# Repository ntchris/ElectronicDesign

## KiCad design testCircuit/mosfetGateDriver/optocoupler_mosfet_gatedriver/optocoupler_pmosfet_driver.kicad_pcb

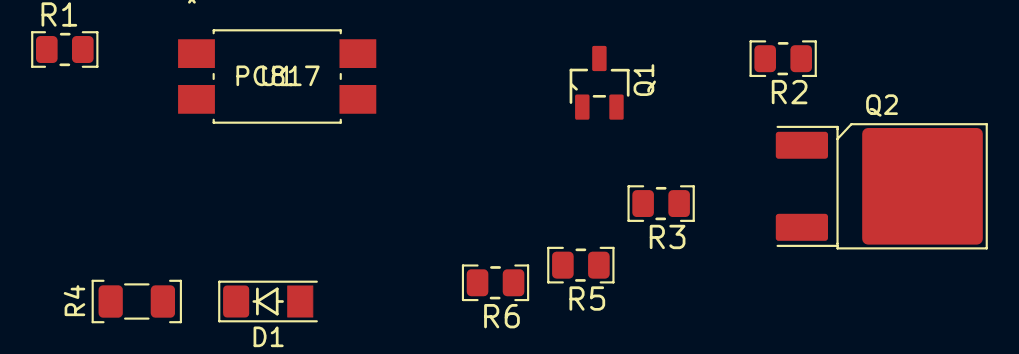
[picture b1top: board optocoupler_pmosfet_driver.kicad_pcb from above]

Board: 2 copper layers, 10 parts (0 on the bottom side), 9 nets, no tracks yet.

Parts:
D1: zener 5.1V; D_MiniMELF_Handsoldering_Zener
Q1: S9013; SOT-23_PNP_NPN
Q2: AOD403_pmosfet; TO-252-2
R1: 510; R_C_0805_2012Metric_Pad1.20x1.50mm_HandSolder
R2: 1.5k; R_C_0805_2012Metric_Pad1.20x1.50mm_HandSolder
R3: 20k; R_C_0805_2012Metric_Pad1.20x1.50mm_HandSolder
R4: 1.5k; R_C_1206_3216Metric_Pad1.33x1.80mm_HandSolder
R5: 800; R_C_0805_2012Metric_Pad1.20x1.50mm_HandSolder
R6: 10k; R_C_0805_2012Metric_Pad1.20x1.50mm_HandSolder
U1: PC817; EL817S1CTU-F

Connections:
/test_point_base: Q1.B, R3.1, U1.3
/test_point_gate: D1.1 (K), Q2.G, R2.1, R4.1
/test_point_load_power: Q2.D, R6.2
GND: Q1.E, R3.2, R6.1
unnamed: D1.2 (A), R5.2
unnamed: Q2.S, R4.2
unnamed: Q1.C, R5.1
unnamed: R1.1, U1.1
unnamed: R2.2, U1.4

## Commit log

2016-10-16 :lollipop: Added .gitattributes & .gitignore files
2017-01-27 submit all ee design
2017-02-04 done
2017-02-27 Finish TL494 design
2017-06-09 commit june 08 2017
2017-06-09 remove export svg
2017-06-09 fix pic
2017-06-09 pic update
2017-06-12 PCB rev2
2017-07-02 add tp5410 and tp4056 design
2017-07-03 5410 and 4056 to print
2017-07-06 folder reorg
2017-08-14 charge boot update
2017-08-27 tl494 new project
2017-08-27 aug27 design PCB finished
2017-08-28 minnor fix
2017-08-28 minor updat 2
2017-08-31 update pcb
2017-10-08 ip5306 charge boost project
2017-10-08 modify inductor 7mm foot print
2017-10-08 modify inductor 7 ver2
2017-10-08 modify inductor7 ver3
2017-10-08 pcb update
2017-10-08 pcb bottom
2017-10-12 IP5306 version 2
2017-10-12 update usb hole position
2017-10-26 add new project ne555 motor pwm controller
2017-10-29 fix the wrong ifrf1205 footprint (source must be ground pin3)
2017-11-05 FP6719_BoostQC submit
2017-11-16 update the cap and pcb
    larger cap in input, add resistor for big cap in output.
    pcb make larger ground around chip to improve heat sink
2017-12-23 555 boost
2017-12-25 IR_dim_light
2017-12-29 create ver8
2018-01-20 tm1637module
2018-01-23 submit all
2018-11-24 submit a lot
2022-11-29 added mosfet gate driver test and scope pic
2022-11-29 submit my kicad lib symbol and footprints

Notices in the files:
parts and their libraries:
Copyright 2021 Accelerated Designs. All rights reserved.
